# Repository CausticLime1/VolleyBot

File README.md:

CAD Files found here:
https://cad.onshape.com/documents/b71e7f16a9ce3487396680f0/w/fcb58f0d3edd17ba5ccc9372/e/33c9d645b66e250968ced99f?renderMode=0&uiState=683ad6bc384832629945b09d

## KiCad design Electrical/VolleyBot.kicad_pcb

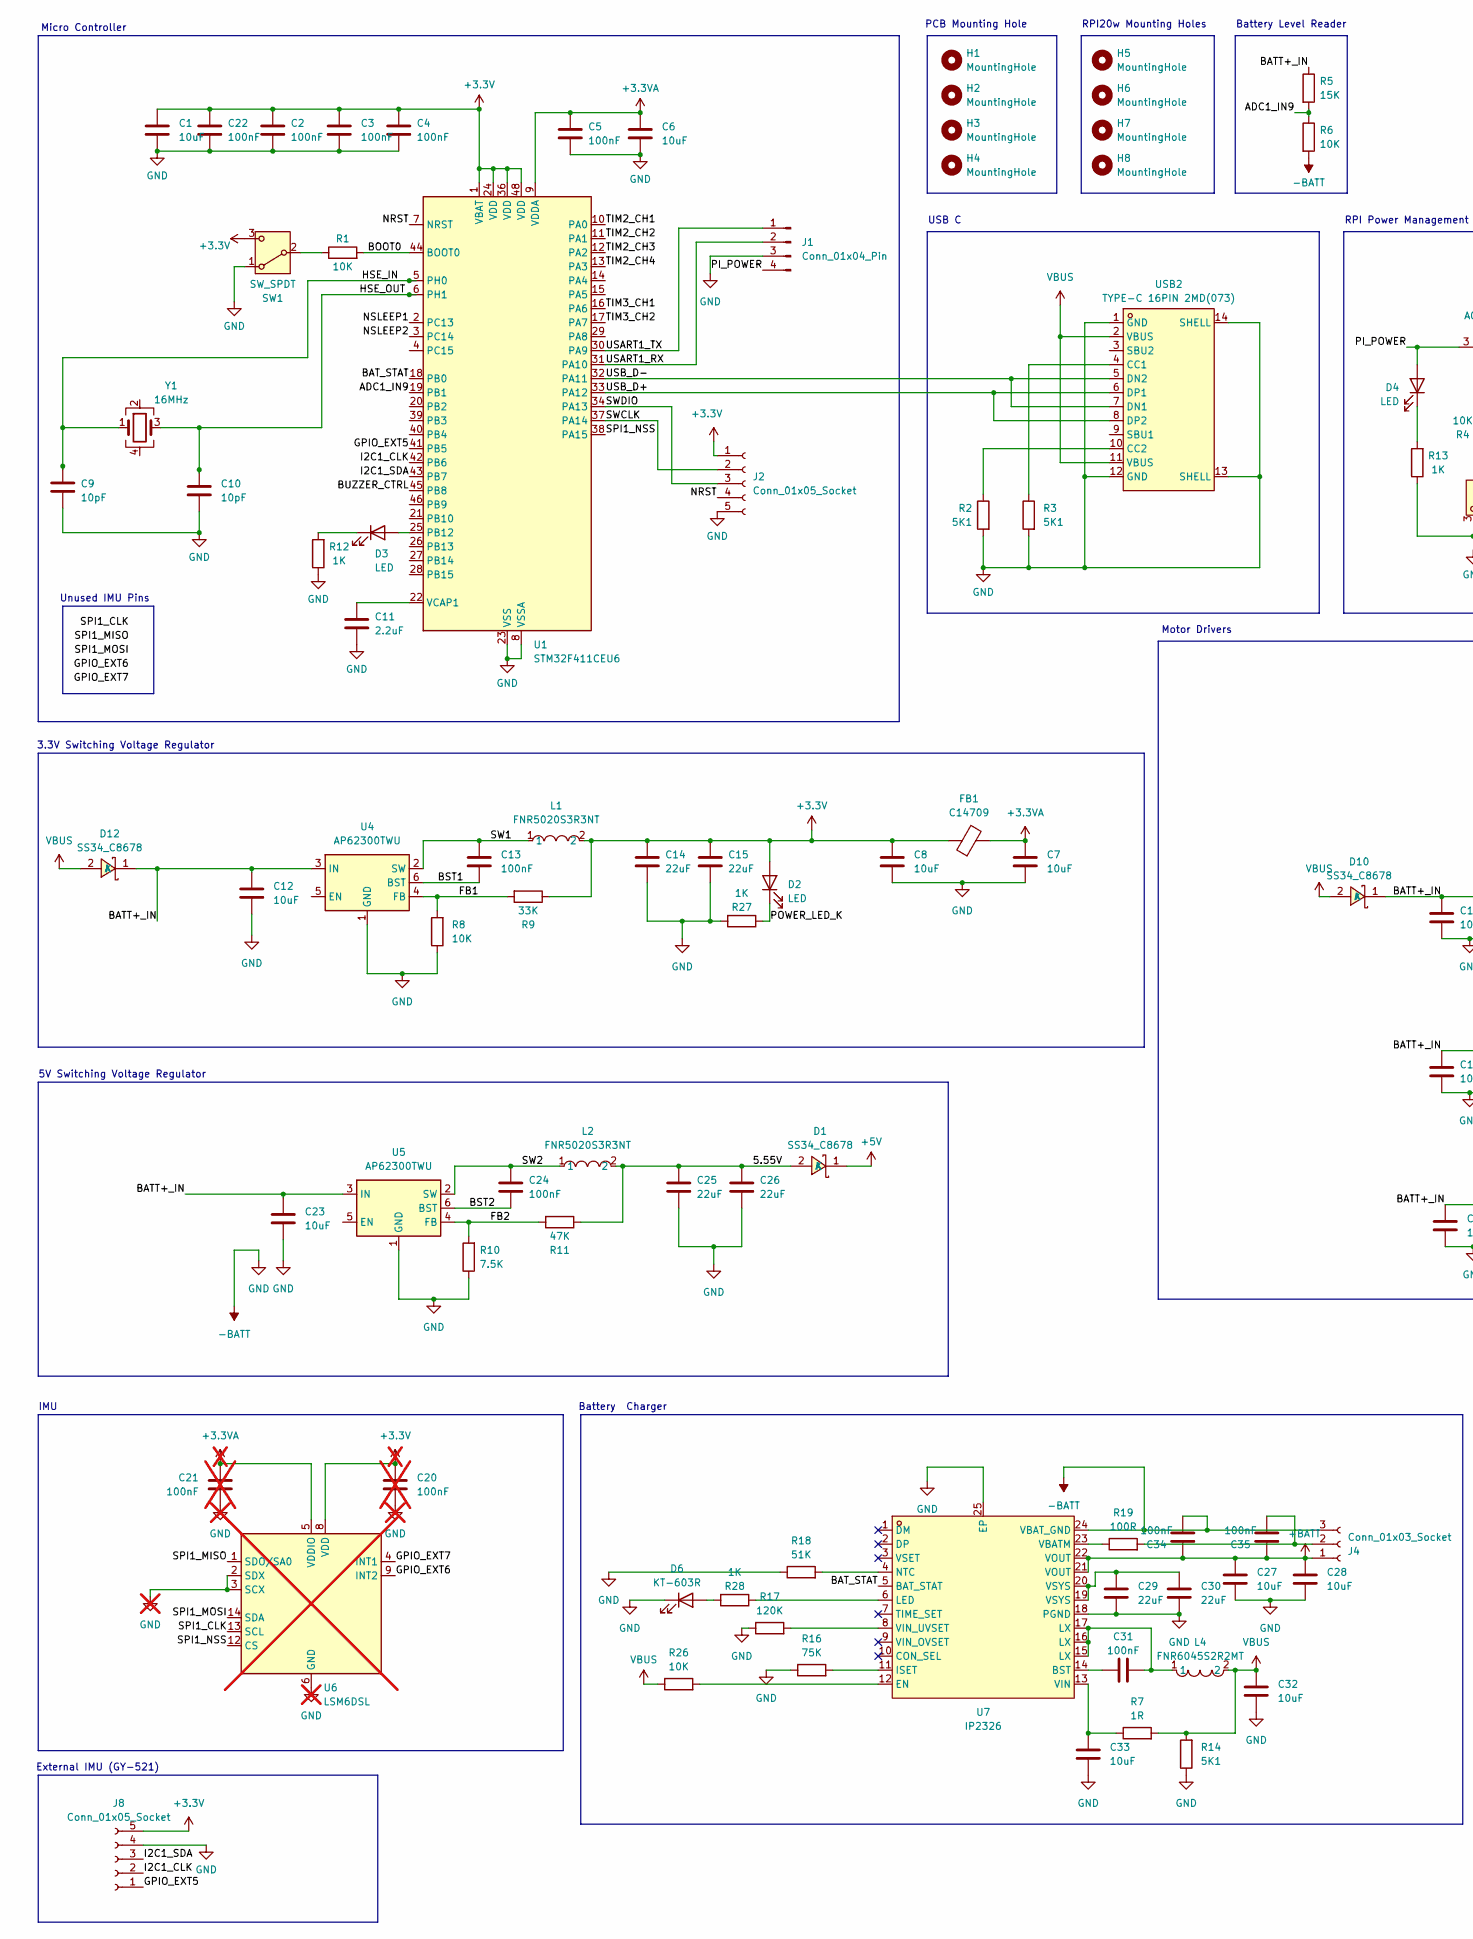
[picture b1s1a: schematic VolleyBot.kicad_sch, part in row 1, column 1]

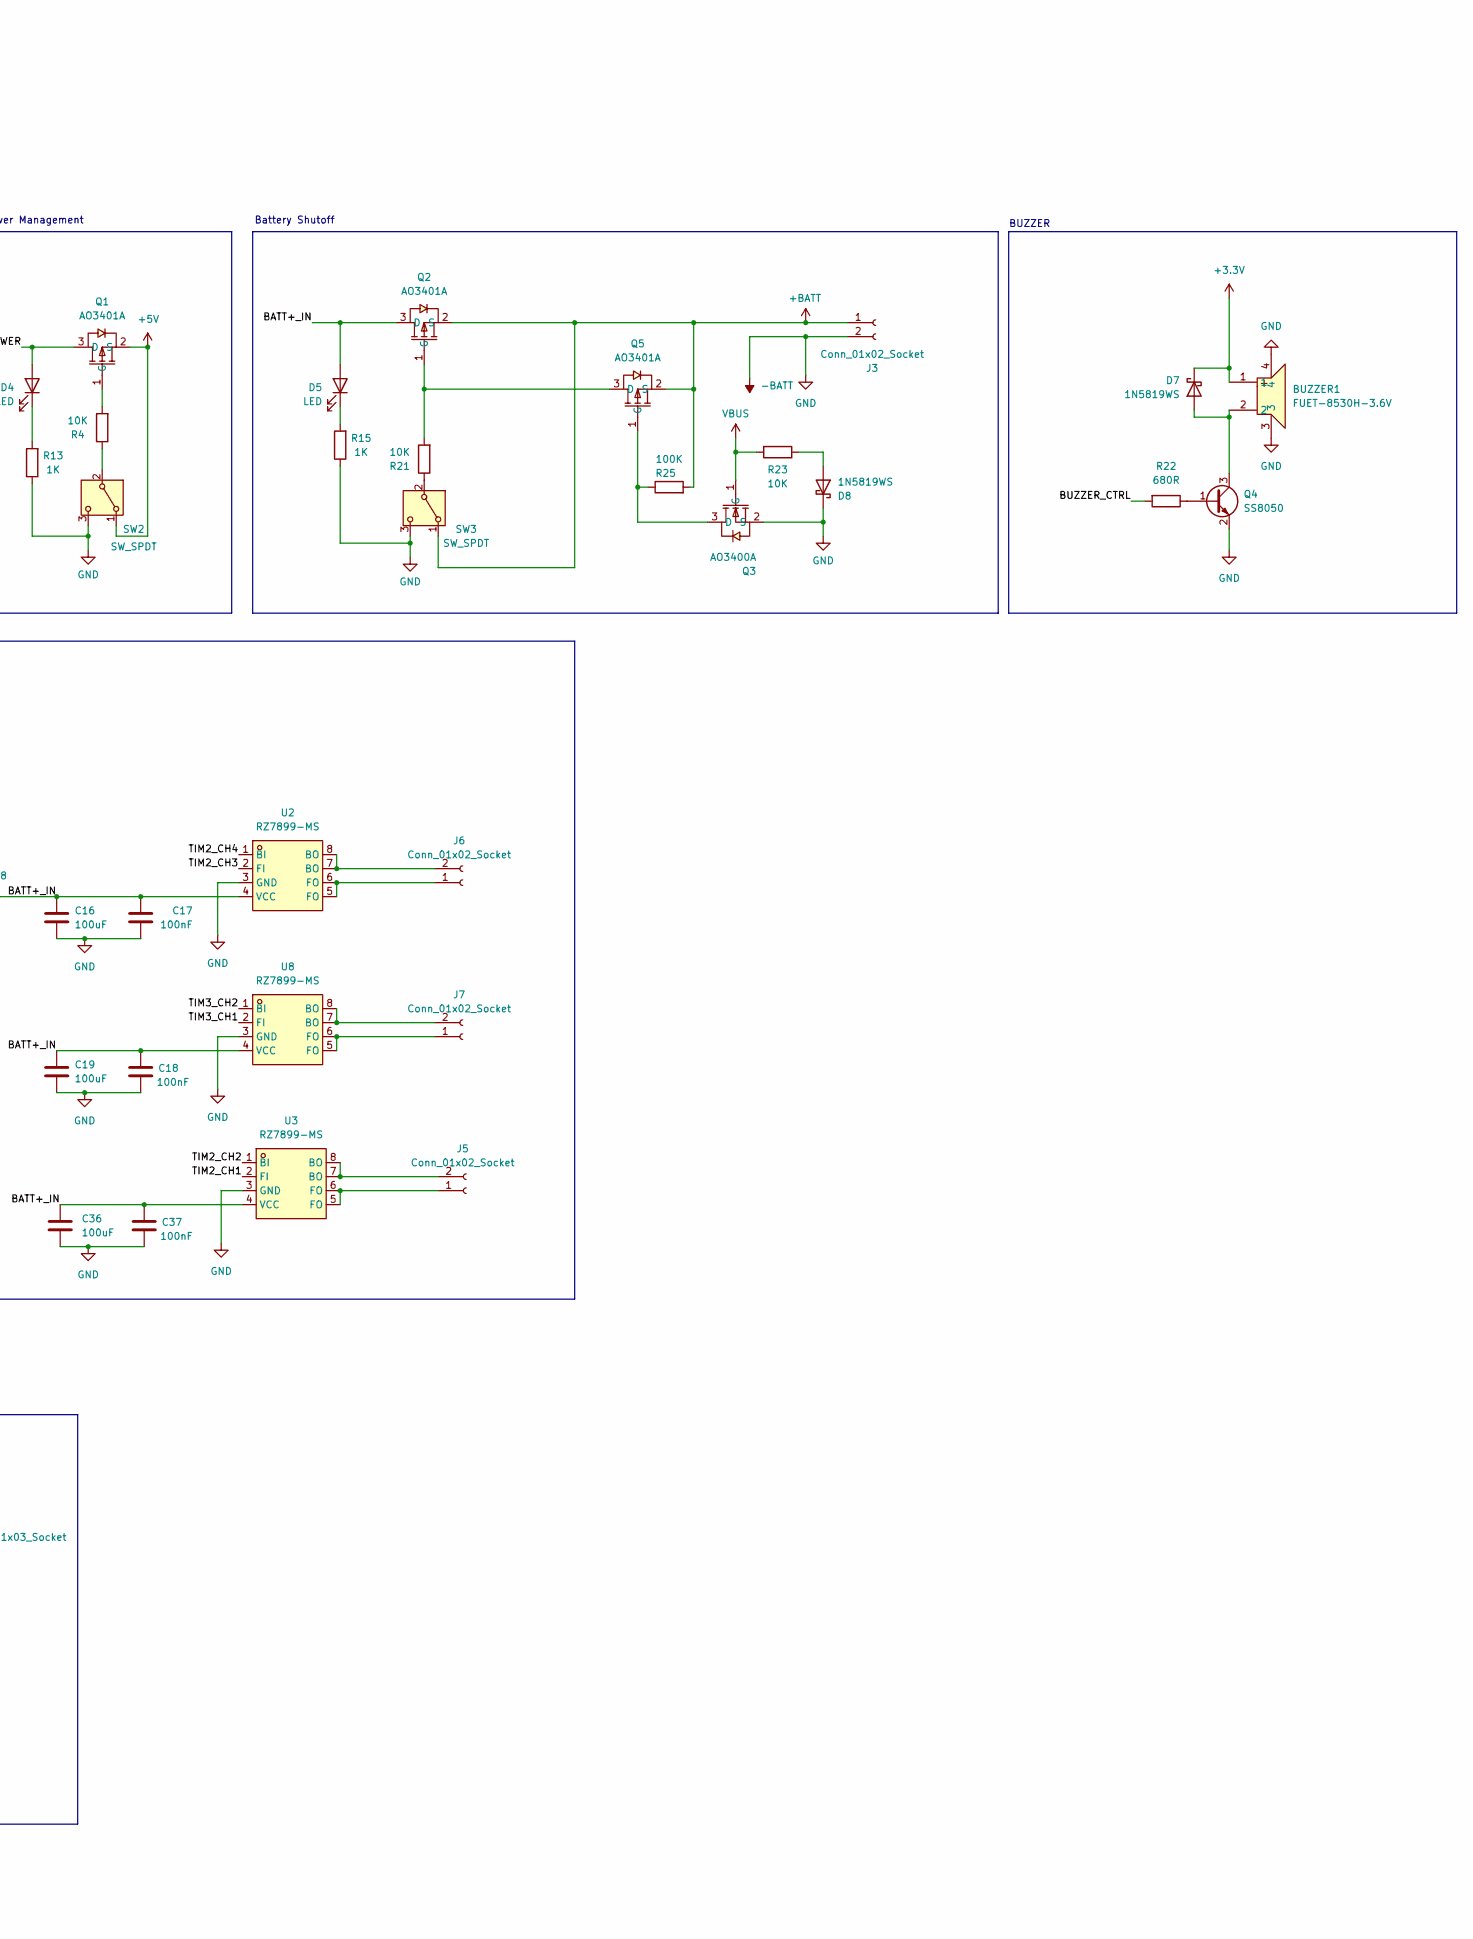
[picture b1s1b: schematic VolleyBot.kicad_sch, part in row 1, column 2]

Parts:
BUZZER1: FUET-8530H-3.6V; BUZ-SMD_4P-L8.5-W8.5_FUET-8530-05; LCSC Part C417429
C1, C6, C12, C23, C27, C28, C32, C33: 10uF; C_0603_1608Metric
C2, C3, C4, C5, C13, C17, C18, C22, C24, C31, C34, C35, C37: 100nF; C_0402_1005Metric
C7, C8: 10uF; C_0805_2012Metric
C9, C10: 10pF; C_0402_1005Metric
C11: 2.2uF; C_0402_1005Metric
C14, C15, C25, C26, C29, C30: 22uF; C_0805_2012Metric
C16, C19, C36: 100uF; C_1206_3216Metric
C20, C21: 100nF; C_0402_1005Metric; not fitted
D1, D10, D12: SS34_C8678; SMA_L4.3-W2.6-LS5.2-RD; LCSC Part C8678
D2, D3, D4, D5: LED; LED_0603_1608Metric
D6: KT-603R; LED_0603_1608Metric
D7, D8: 1N5819WS; D_SOD-323
FB1: C14709; L_0603_1608Metric
H1, H2, H3, H4: MountingHole; MountingHole_2.2mm_M2
H5, H6, H7, H8: MountingHole; MountingHole_2.7mm_M2.5
J1: Conn_01x04_Pin; PinHeader_1x04_P2.54mm_Vertical
J2, J8: Conn_01x05_Socket; JST_XH_S5B-XH-A_1x05_P2.50mm_Horizontal
J3: Conn_01x02_Socket; AMASS_XT60PW-F_1x02_P7.20mm_Horizontal
J4: Conn_01x03_Socket; JST_XH_S3B-XH-A_1x03_P2.50mm_Horizontal
J5, J6, J7: Conn_01x02_Socket; JST_XH_S2B-XH-A_1x02_P2.50mm_Horizontal
L1, L2: FNR5020S3R3NT; IND-SMD_L5.0-W5.0_FNR50XXS; LCSC Part C167926
L4: FNR6045S2R2MT; IND-SMD_L6.0-W6.0_FNR60XXS; LCSC Part C168059
Q1, Q2, Q5: AO3401A; SOT-23_L2.9-W1.3-P1.90-LS2.4-BR; LCSC Part C15127
Q3: AO3400A; SOT-23-3_L2.9-W1.3-P1.90-LS2.4-BR; LCSC Part C20917
Q4: SS8050; SOT-23
R1, R4, R6, R8, R21, R23, R26: 10K; R_0402_1005Metric
R2, R3, R14: 5K1; R_0402_1005Metric
R5: 15K; R_0402_1005Metric
R7: 1R; R_0603_1608Metric
R9: 33K; R_0402_1005Metric
R10: 7.5K; R_0603_1608Metric
R11: 47K; R_0603_1608Metric
R12, R13, R15, R27, R28: 1K; R_0402_1005Metric
R16: 75K; R_0603_1608Metric
R17: 120K; R_0603_1608Metric
R18: 51K; R_0603_1608Metric
R19: 100R; R_1206_3216Metric
R22: 680R; R_0603_1608Metric
R25: 100K; R_0603_1608Metric
SW1, SW2, SW3: SW_SPDT; SW_SPDT_PCM12
U1: STM32F411CEU6; QFN-48-1EP_7x7mm_P0.5mm_EP5.6x5.6mm
U2, U3, U8: RZ7899-MS; SOIC-8_L4.9-W3.9-P1.27-LS6.0-BL; LCSC Part C22462553
U4, U5: AP62300TWU; TSOT-23-6
U6: LSM6DSL; LGA-14_3x2.5mm_P0.5mm_LayoutBorder3x4y; not fitted
U7: IP2326; VQFN-24_L4.0-W4.0-P0.50-BL-EP2.5; LCSC Part C2832094
USB2: TYPE-C 16PIN 2MD(073); USB-C-SMD_TYPE-C-6PIN-2MD-073; LCSC Part C2765186
Y1: 16MHz; Crystal_SMD_3225-4Pin_3.2x2.5mm

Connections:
+3.3V: BUZZER1.1, C1.1, C2.1, C3.1, C4.1, C8.1, C14.1, C15.1, C20.1, C22.1, D2.2 (A), D7.1 (K), FB1.1, J2.1, J8.5, L1.2, R9.1, SW1.3 (C), U1.1 (VBAT), U1.24 (VDD), U1.36 (VDD), U1.48 (VDD), U6.8 (VDD)
+3.3VA: C5.1, C6.1, C7.1, C21.1, FB1.2, U1.9 (VDDA), U6.5 (VDDIO)
+5V: D1.1 (K), Q1.2 (S), SW2.1 (A)
+BATT: C27.1, C28.1, C34.1, C35.1, J3.1, J4.1, Q2.2 (S), Q5.2 (S), R25.2, SW3.1 (A), U7.21 (VOUT), U7.22 (VOUT)
-BATT: BUZZER1.3, BUZZER1.4, C1.2, C2.2, C3.2, C4.2, C5.2, C6.2, C7.2, C8.2, C9.2, C10.2, C11.2, C12.2, C14.2, C15.2, C16.2, C17.2, C18.2, C19.2, C20.2, C21.2, C22.2, C23.2, C25.2, C26.2, C27.2, C28.2, C29.2, C30.2, C32.2, C33.2, C34.2, C36.2, C37.2, D6.1 (K), D8.1 (K), J1.3, J2.5, J3.2, J4.3, J8.4, Q3.2 (S), Q4.2 (E), R2.2, R3.2, R6.2, R8.1, R10.1, R12.1, R13.1, R14.1, R15.1, R16.1, R17.1, R18.1, R27.2, SW1.1 (A), SW2.3 (C), SW3.3 (C), U1.8 (VSSA), U1.23 (VSS), U1.35 (VSS), U1.47 (VSS), U1.49 (VSS), U2.3 (GND), U3.3 (GND), U4.1 (GND), U5.1 (GND), U6.2 (SDX), U6.3 (SCX), U6.6 (GND), U6.7 (GND), U7.18 (PGND), U7.24 (VBAT_GND), U7.25 (EP), U8.3 (GND), USB2.1 (GND), USB2.12 (GND), USB2.13 (SHELL), USB2.14 (SHELL)
/5.55V: C25.1, C26.1, D1.2 (A), L2.2, R11.1
/ADC1_IN9: R5.2, R6.1, U1.19 (PB1)
/BATT+_IN: C12.1, C16.1, C17.1, C18.1, C19.1, C23.1, C36.1, C37.1, D5.2 (A), D10.1 (K), D12.1 (K), Q2.3 (D), R5.1, U2.4 (VCC), U3.4 (VCC), U4.3 (IN), U5.3 (IN), U8.4 (VCC)
/BAT_STAT: U1.18 (PB0), U7.5 (BAT_STAT)
/BOOT0: R1.2, U1.44 (BOOT0)
/BST1: C13.1, U4.6 (BST)
/BST2: C24.1, U5.6 (BST)
/BUZZER_CTRL: R22.2, U1.45 (PB8)
/FB1: R8.2, R9.2, U4.4 (FB)
/FB2: R10.2, R11.2, U5.4 (FB)
/GPIO_EXT5: J8.1, U1.41 (PB5)
/HSE_IN: C9.1, U1.5 (PH0), Y1.1
/HSE_OUT: C10.1, U1.6 (PH1), Y1.3
/I2C1_CLK: J8.2, U1.42 (PB6)
/I2C1_SDA: J8.3, U1.43 (PB7)
/NRST: J2.4, U1.7 (NRST)
/NSLEEP1: U1.2 (PC13)
/NSLEEP2: U1.3 (PC14)
/PI_POWER: D4.2 (A), J1.4, Q1.3 (D)
/POWER_LED_K: D2.1 (K), R27.1
/SPI1_NSS: U1.38 (PA15), U6.12 (CS)
/SW1: C13.2, L1.1, U4.2 (SW)
/SW2: C24.2, L2.1, U5.2 (SW)
/SWCLK: J2.2, U1.37 (PA14)
/SWDIO: J2.3, U1.34 (PA13)
/TIM2_CH1: U1.10 (PA0), U3.2 (FI)
/TIM2_CH2: U1.11 (PA1), U3.1 (BI)
/TIM2_CH3: U1.12 (PA2), U2.2 (FI)
/TIM2_CH4: U1.13 (PA3), U2.1 (BI)
/TIM3_CH1: U1.16 (PA6), U8.2 (FI)
/TIM3_CH2: U1.17 (PA7), U8.1 (BI)
/USART1_RX: J1.2, U1.31 (PA10)
/USART1_TX: J1.1, U1.30 (PA9)
/USB_D+: U1.33 (PA12), USB2.6 (DP1), USB2.8 (DP2)
/USB_D-: U1.32 (PA11), USB2.5 (DN2), USB2.7 (DN1)
unnamed: C29.1, C30.1, U7.19 (VSYS), U7.20 (VSYS)
unnamed: C31.2, L4.1, U7.15 (LX), U7.16 (LX), U7.17 (LX)
unnamed: D3.2 (A), U1.25 (PB12)
unnamed: D3.1 (K), R12.2
unnamed: D4.1 (K), R13.2
unnamed: D5.1 (K), R15.2
unnamed: D6.2 (A), R28.2
unnamed: BUZZER1.2, D7.2 (A), Q4.3 (C)
unnamed: D8.2 (A), R23.1
unnamed: C35.2, J4.2, R19.2
unnamed: J5.1, U3.5 (FO), U3.6 (FO)
unnamed: J5.2, U3.7 (BO), U3.8 (BO)
unnamed: J6.1, U2.5 (FO), U2.6 (FO)
unnamed: J6.2, U2.7 (BO), U2.8 (BO)
unnamed: J7.1, U8.5 (FO), U8.6 (FO)
unnamed: J7.2, U8.7 (BO), U8.8 (BO)
unnamed: Q1.1 (G), R4.2
unnamed: Q2.1 (G), Q5.3 (D), R21.2
unnamed: Q3.3 (D), Q5.1 (G), R25.1
unnamed: Q4.1 (B), R22.1
unnamed: R1.1, SW1.2 (B)
unnamed: R4.1, SW2.2 (B)
unnamed: R21.1, SW3.2 (B)
unnamed: C11.1, U1.22 (VCAP1)
unnamed: C31.1, U7.14 (BST)
unnamed: R26.2, U7.12 (EN)
unnamed: R16.2, U7.11 (ISET)
unnamed: R28.1, U7.6 (LED)
unnamed: R18.2, U7.4 (NTC)
unnamed: R19.1, U7.23 (VBATM)
unnamed: C33.1, R7.1, U7.13 (VIN)
unnamed: R17.2, U7.8 (VIN_UVSET)
unnamed: R3.1, USB2.4 (CC1)
unnamed: R2.1, USB2.10 (CC2)
VBUS: C32.1, D10.2 (A), D12.2 (A), L4.2, Q3.1 (G), R7.2, R14.2, R23.2, R26.1, USB2.2 (VBUS), USB2.11 (VBUS)

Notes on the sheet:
External IMU (GY-521)
IMU
Unused IMU Pins
BUZZER
5V Switching Voltage Regulator
Battery Shutoff
Battery Level Reader
RPI Power Management
3.3V Switching Voltage Regulator
Micro Controller
RPI20w Mounting Holes
PCB Mounting Hole
Battery Charger
Motor Drivers
USB C

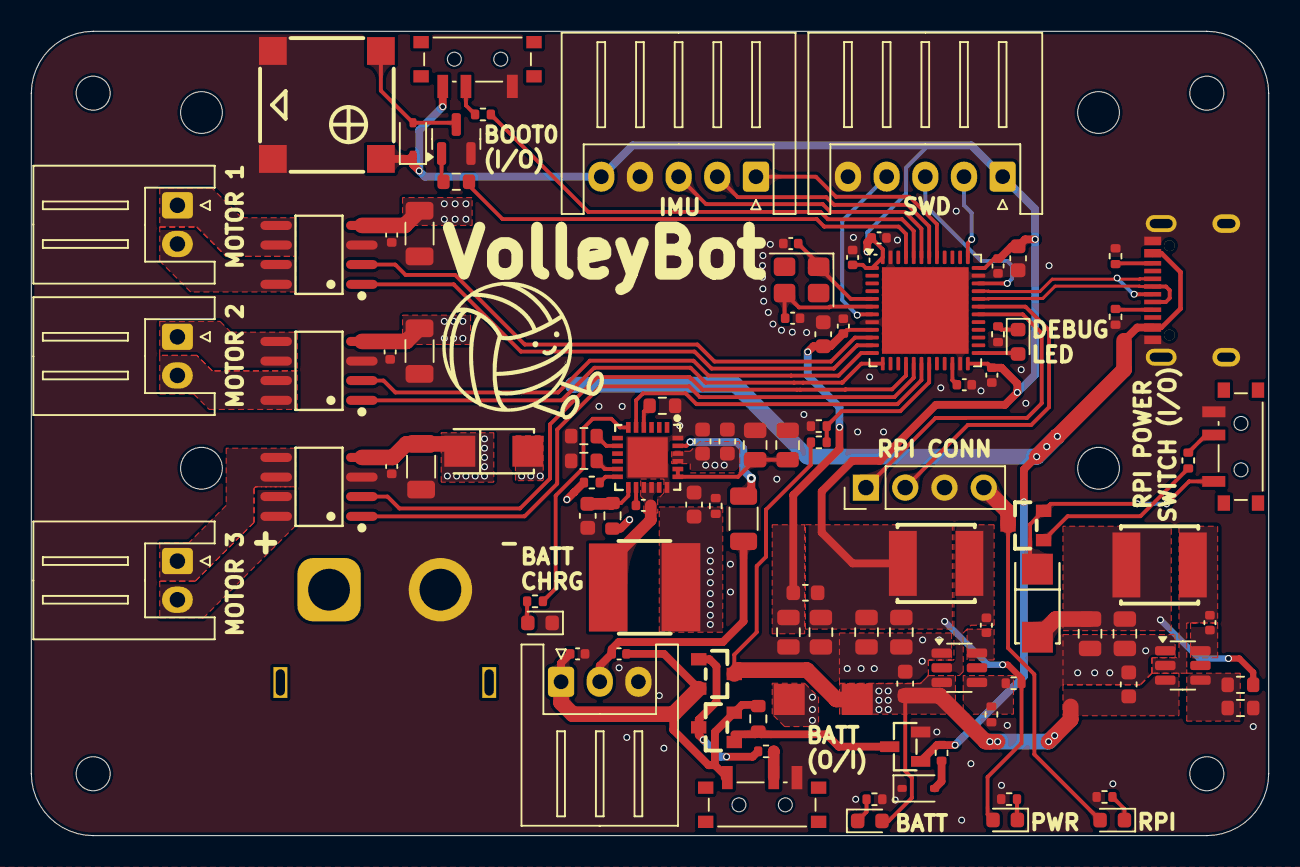
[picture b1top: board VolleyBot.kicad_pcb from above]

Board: 2 copper layers, 80.0 x 52.0 mm, 109 parts (0 on the bottom side), 72 nets.

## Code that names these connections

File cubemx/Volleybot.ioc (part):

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Mcu.Name=STM32F411C(C-E)Ux
Mcu.Package=UFQFPN48
Mcu.UserName=STM32F411CEUx
PA0-WKUP.Signal=S_TIM2_CH1_ETR
PA1.Signal=S_TIM2_CH2
PA10.Mode=Asynchronous
PA10.Signal=USART1_RX
PA11.Mode=Device_Only
PA11.Signal=USB_OTG_FS_DM
PA12.Mode=Device_Only
PA12.Signal=USB_OTG_FS_DP
PA13.Mode=Serial_Wire
PA13.Signal=SYS_JTMS-SWDIO
PA14.Mode=Serial_Wire
PA14.Signal=SYS_JTCK-SWCLK
PA2.Signal=S_TIM2_CH3
PA3.Signal=S_TIM2_CH4
PA6.Signal=S_TIM3_CH1
PA7.Signal=S_TIM3_CH2
PA9.Mode=Asynchronous
PA9.Signal=USART1_TX
PB0.Signal=GPIO_Input
PB1.Signal=ADCx_IN9
PB10.Signal=GPIO_Input
PB12.Signal=GPIO_Output
PB5.Signal=GPXTI5
PB6.Mode=I2C
PB6.Signal=I2C1_SCL
PB7.Mode=I2C
PB7.Signal=I2C1_SDA
PB9.Signal=S_TIM4_CH4
PC13-ANTI_TAMP.Signal=GPIO_Output
PC14-OSC32_IN.Signal=GPIO_Output
PH0\ -\ OSC_IN.Mode=HSE-External-Oscillator
PH0\ -\ OSC_IN.Signal=RCC_OSC_IN
PH1\ -\ OSC_OUT.Mode=HSE-External-Oscillator
PH1\ -\ OSC_OUT.Signal=RCC_OSC_OUT
RCC.HSE_VALUE=16000000
RCC.SYSCLKFreq_VALUE=16000000
board=custom

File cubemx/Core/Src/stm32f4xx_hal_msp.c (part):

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
    __HAL_RCC_GPIOB_CLK_ENABLE();
    /**I2C1 GPIO Configuration
    PB6     ------> I2C1_SCL
    PB7     ------> I2C1_SDA
    */
    GPIO_InitStruct.Pin = GPIO_PIN_6|GPIO_PIN_7;
    GPIO_InitStruct.Mode = GPIO_MODE_AF_OD;
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    __HAL_RCC_I2C1_CLK_DISABLE();

    /**I2C1 GPIO Configuration
    PB6     ------> I2C1_SCL
    PB7     ------> I2C1_SDA
    */
    HAL_GPIO_DeInit(GPIOB, GPIO_PIN_6);

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    /* USER CODE END TIM2_MspPostInit 0 */
    __HAL_RCC_GPIOA_CLK_ENABLE();
    /**TIM2 GPIO Configuration
    PA1     ------> TIM2_CH2
    PA2     ------> TIM2_CH3
    PA3     ------> TIM2_CH4
    PA5     ------> TIM2_CH1
    */
    GPIO_InitStruct.Pin = GPIO_PIN_1|GPIO_PIN_2|GPIO_PIN_3|GPIO_PIN_5;
    GPIO_InitStruct.Mode = GPIO_MODE_AF_PP;
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
    __HAL_RCC_GPIOA_CLK_ENABLE();
    /**TIM3 GPIO Configuration
    PA6     ------> TIM3_CH1
    PA7     ------> TIM3_CH2
    */
    GPIO_InitStruct.Pin = GPIO_PIN_6|GPIO_PIN_7;
    GPIO_InitStruct.Mode = GPIO_MODE_AF_PP;
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
    __HAL_RCC_GPIOA_CLK_ENABLE();
    /**USART1 GPIO Configuration
    PA9     ------> USART1_TX
    PA10     ------> USART1_RX
    */
    GPIO_InitStruct.Pin = GPIO_PIN_9|GPIO_PIN_10;
    GPIO_InitStruct.Mode = GPIO_MODE_AF_PP;
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    __HAL_RCC_USART1_CLK_DISABLE();

    /**USART1 GPIO Configuration
    PA9     ------> USART1_TX
    PA10     ------> USART1_RX
    */
    HAL_GPIO_DeInit(GPIOA, GPIO_PIN_9|GPIO_PIN_10);

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
    __HAL_RCC_GPIOA_CLK_ENABLE();
    /**USB_OTG_FS GPIO Configuration
    PA11     ------> USB_OTG_FS_DM
    PA12     ------> USB_OTG_FS_DP
    */
    GPIO_InitStruct.Pin = GPIO_PIN_11|GPIO_PIN_12;
    GPIO_InitStruct.Mode = GPIO_MODE_AF_PP;
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    __HAL_RCC_USB_OTG_FS_CLK_DISABLE();

    /**USB_OTG_FS GPIO Configuration
    PA11     ------> USB_OTG_FS_DM
    PA12     ------> USB_OTG_FS_DP
    */
    HAL_GPIO_DeInit(GPIOA, GPIO_PIN_11|GPIO_PIN_12);

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
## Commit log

2025-06-01 routed pcb
2025-06-02 pcb made
2025-06-03 correction of manufacturing files
2025-11-30 bat charge
2025-11-30 schem done
2025-12-02 final V2
2025-12-04 manufacturing
2025-12-17 code test
2025-12-17 updated startup code
2025-12-18 updated RTOS
2025-12-20 winter break push
2025-12-29 starting to move to FreeRTOS
2026-01-18 code

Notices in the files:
cubemx/Core/Src/stm32f4xx_hal_msp.c:
Copyright (c) 2025 STMicroelectronics.
All rights reserved.
This software is licensed under terms that can be found in the LICENSE file
